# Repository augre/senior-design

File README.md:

senior-design
=============

arduino code, schematics, board layout

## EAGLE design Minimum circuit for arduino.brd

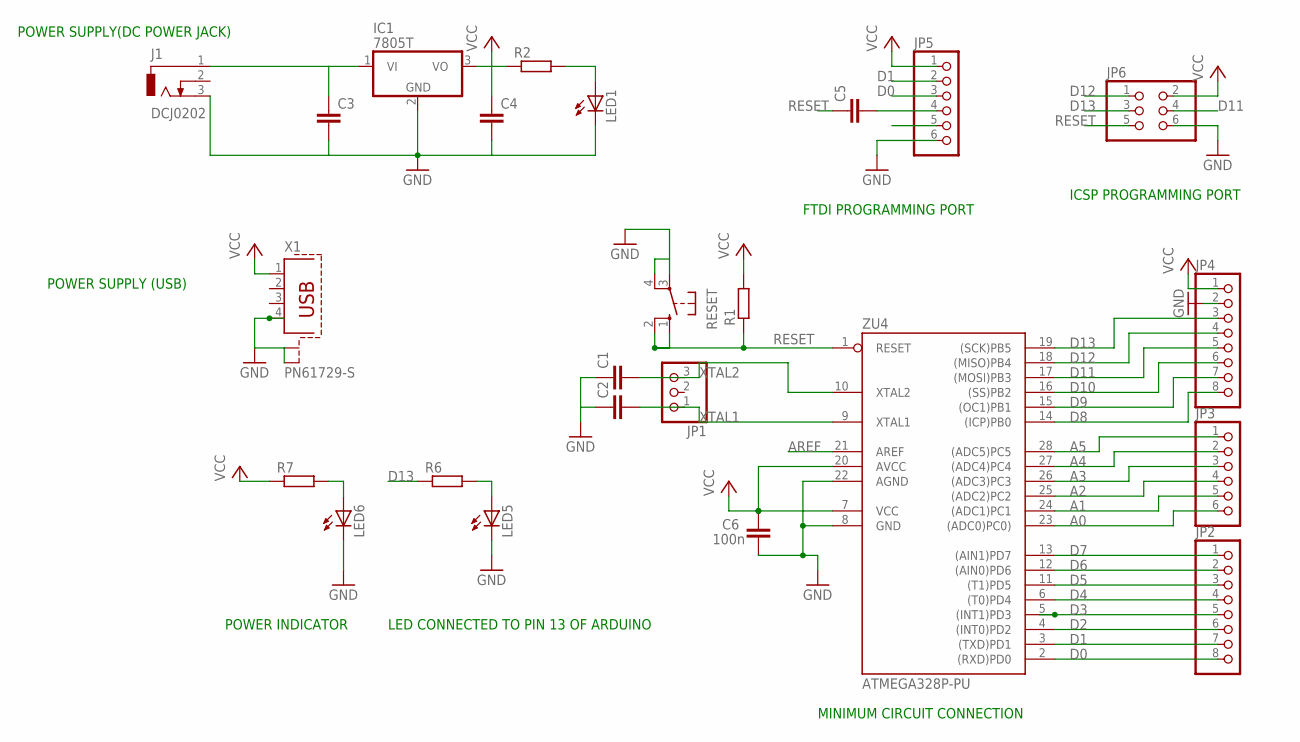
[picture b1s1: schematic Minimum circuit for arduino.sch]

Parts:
C1, C2: C2.5/6; C2.5-6
C3, C4, C5: C2.5/5; C2.5-5
C6: 100n; C2.5-4
IC1: 7805T; TO220H
J1: DCJ0202
JP1: PINHD-1X3; 1X03
JP2, JP4: PINHD-1X8; 1X08
JP3, JP5: PINHD-1X6; 1X06
JP6: PINHD-2X3; 2X03
LED1, LED5, LED6: LED5MM
R1: R-EU_0309/12; 0309/12
R2, R6, R7: R-EU_0207/10; 0207/10
RESET: 10-XX; B3F-10XX
X1: PN61729-S
ZU4: ATMEGA328P-PU; DIL28-3

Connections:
A0: JP3.6, ZU4.23 ((ADC0)PC0))
A1: JP3.5, ZU4.24 ((ADC1)PC1)
A2: JP3.4, ZU4.25 ((ADC2)PC2)
A3: JP3.3, ZU4.26 ((ADC3)PC3)
A4: JP3.2, ZU4.27 ((ADC4)PC4)
A5: JP3.1, ZU4.28 ((ADC5)PC5)
AREF: ZU4.21 (AREF)
D0: JP2.8, JP5.3, ZU4.2 ((RXD)PD0)
D1: JP2.7, JP5.2, ZU4.3 ((TXD)PD1)
D2: JP2.6, ZU4.4 ((INT0)PD2)
D3: JP2.5, ZU4.5 ((INT1)PD3)
D4: JP2.4, ZU4.6 ((T0)PD4)
D5: JP2.3, ZU4.11 ((T1)PD5)
D6: JP2.2, ZU4.12 ((AIN0)PD6)
D7: JP2.1, ZU4.13 ((AIN1)PD7)
D8: JP4.8, ZU4.14 ((ICP)PB0)
D9: JP4.7, ZU4.15 ((OC1)PB1)
D10: JP4.6, ZU4.16 ((SS)PB2)
D11: JP4.5, JP6.4, ZU4.17 ((MOSI)PB3)
D12: JP4.4, JP6.1, ZU4.18 ((MISO)PB4)
D13: JP4.3, JP6.3, R6.1, ZU4.19 ((SCK)PB5)
GND: C1.1, C2.1, C3.2, C4.2, C6.1, IC1.2 (GND), J1.3, JP4.2, JP5.6, JP6.6, LED1.K (C), LED5.K (C), LED6.K (C), RESET.3, RESET.4 (P1), X1.4, X1.S1, X1.S2, ZU4.8 (GND), ZU4.22 (AGND)
unnamed: C6.2, ZU4.7 (VCC), ZU4.20 (AVCC)
unnamed: C3.1, IC1.1 (VI), J1.1
unnamed: LED1.A, R2.2
unnamed: LED5.A, R6.2
unnamed: LED6.A, R7.2
unnamed: C5.2, JP5.4
RESET: C5.1, JP6.5, R1.1, RESET.1 (S), RESET.2 (S1), ZU4.1 (RESET)
VCC: C4.1, IC1.3 (VO), JP4.1, JP5.1, JP6.2, R1.2, R2.1, R7.1, X1.1
XTAL1: C2.2, JP1.1, ZU4.9 (XTAL1)
XTAL2: C1.2, JP1.3, ZU4.10 (XTAL2)

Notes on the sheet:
POWER INDICATOR
LED CONNECTED TO PIN 13 OF ARDUINO
POWER SUPPLY(DC POWER JACK)
POWER SUPPLY (USB)
FTDI PROGRAMMING PORT
ICSP PROGRAMMING PORT
MINIMUM CIRCUIT CONNECTION

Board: 2 copper layers, 24 parts (0 on the bottom side), 31 nets, no tracks yet.

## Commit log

2013-09-17 Revert "Initial commit"
    This reverts commit 8b4362553fd3497c6e523d20e1ee845df434840e.
2013-09-17 Original file from Mark
    Might be a bit more than you want, search for TCCR2A, TCCR2B, OCR2A, and
    basically anything that has to do with timer2.
2013-09-17 The circuit schematic we need as minimum
    need to add the motor driver ic-s and a 'plug in' socket for the
    bluetooth
2013-09-17 The pin out of the layout should be arduino like!
2013-09-17 38khz interrupt to try out in the lab
2013-11-28 The motors run from the sensor signals
    No bluetooth, yet
2013-11-29 bluetooth added
